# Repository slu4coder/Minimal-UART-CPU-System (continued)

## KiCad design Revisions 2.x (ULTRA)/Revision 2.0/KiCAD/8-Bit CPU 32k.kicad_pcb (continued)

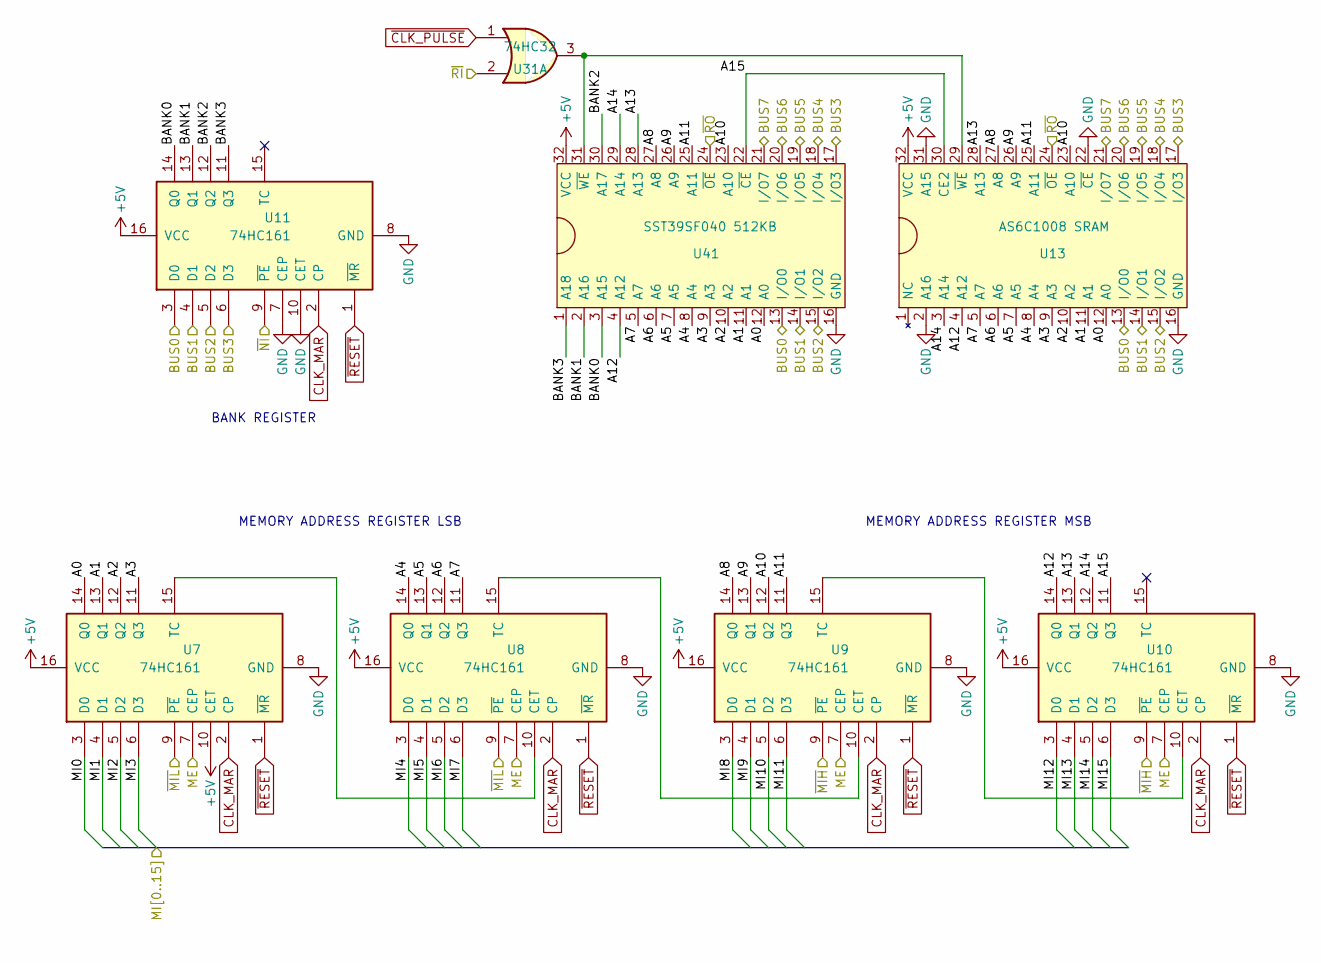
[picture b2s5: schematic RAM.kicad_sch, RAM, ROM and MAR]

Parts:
U7, U8, U9, U10, U11: 74HC161; DIP-16_W7.62mm
U13: AS6C1008 SRAM; DIP-32_W15.24mm
U31: 74HC32; DIP-14_W7.62mm
U41: SST39SF040 512KB; DIP-32_W15.24mm_Socket

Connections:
+5V: U7.10 (CET), U7.16 (VCC), U8.16 (VCC), U9.16 (VCC), U10.16 (VCC), U11.16 (VCC), U13.32 (VCC), U41.32 (VCC); also elsewhere on the board
/ALU/BUS0: U11.3 (D0), U13.13 (I/O0), U41.13 (I/O0); also elsewhere on the board
/ALU/BUS1: U11.4 (D1), U13.14 (I/O1), U41.14 (I/O1); also elsewhere on the board
/ALU/BUS2: U11.5 (D2), U13.15 (I/O2), U41.15 (I/O2); also elsewhere on the board
/ALU/BUS3: U11.6 (D3), U13.17 (I/O3), U41.17 (I/O3); also elsewhere on the board
/ALU/BUS4: U13.18 (I/O4), U41.18 (I/O4); also elsewhere on the board
/ALU/BUS5: U13.19 (I/O5), U41.19 (I/O5); also elsewhere on the board
/ALU/BUS6: U13.20 (I/O6), U41.20 (I/O6); also elsewhere on the board
/ALU/BUS7: U13.21 (I/O7), U41.21 (I/O7); also elsewhere on the board
/Control Logic/ME: U7.7 (CEP), U8.7 (CEP), U9.7 (CEP), U10.7 (CEP); also elsewhere on the board
/Control Logic/~MIH: U9.9 (~PE), U10.9 (~PE); also elsewhere on the board
/Control Logic/~MIL: U7.9 (~PE), U8.9 (~PE); also elsewhere on the board
/Control Logic/~NI: U11.9 (~PE); also elsewhere on the board
/Control Logic/~RI: U31.2; also elsewhere on the board
/Control Logic/~RO: U13.24 (~OE), U41.24 (~OE); also elsewhere on the board
/Memory/A0: U7.14 (Q0), U13.12 (A0), U41.12 (A0)
/Memory/A1: U7.13 (Q1), U13.11 (A1), U41.11 (A1)
/Memory/A2: U7.12 (Q2), U13.10 (A2), U41.10 (A2)
/Memory/A3: U7.11 (Q3), U13.9 (A3), U41.9 (A3)
/Memory/A4: U8.14 (Q0), U13.8 (A4), U41.8 (A4)
/Memory/A5: U8.13 (Q1), U13.7 (A5), U41.7 (A5)
/Memory/A6: U8.12 (Q2), U13.6 (A6), U41.6 (A6)
/Memory/A7: U8.11 (Q3), U13.5 (A7), U41.5 (A7)
/Memory/A8: U9.14 (Q0), U13.27 (A8), U41.27 (A8)
/Memory/A9: U9.13 (Q1), U13.26 (A9), U41.26 (A9)
/Memory/A10: U9.12 (Q2), U13.23 (A10), U41.23 (A10)
/Memory/A11: U9.11 (Q3), U13.25 (A11), U41.25 (A11)
/Memory/A12: U10.14 (Q0), U13.4 (A12), U41.4 (A12)
/Memory/A13: U10.13 (Q1), U13.28 (A13), U41.28 (A13)
/Memory/A14: U10.12 (Q2), U13.3 (A14), U41.29 (A14)
/Memory/A15: U10.11 (Q3), U13.30 (CE2), U41.22 (~CE)
/Memory/BANK0: U11.14 (Q0), U41.3 (A15)
/Memory/BANK1: U11.13 (Q1), U41.2 (A16)
/Memory/BANK2: U11.12 (Q2), U41.30 (A17)
/Memory/BANK3: U11.11 (Q3), U41.1 (A18)
/Memory/MI0: U7.3 (D0); also elsewhere on the board
/Memory/MI1: U7.4 (D1); also elsewhere on the board
/Memory/MI2: U7.5 (D2); also elsewhere on the board
/Memory/MI3: U7.6 (D3); also elsewhere on the board
/Memory/MI4: U8.3 (D0); also elsewhere on the board
/Memory/MI5: U8.4 (D1); also elsewhere on the board
/Memory/MI6: U8.5 (D2); also elsewhere on the board
/Memory/MI7: U8.6 (D3); also elsewhere on the board
/Memory/MI8: U9.3 (D0); also elsewhere on the board
/Memory/MI9: U9.4 (D1); also elsewhere on the board
/Memory/MI10: U9.5 (D2); also elsewhere on the board
/Memory/MI11: U9.6 (D3); also elsewhere on the board
/Memory/MI12: U10.3 (D0); also elsewhere on the board
/Memory/MI13: U10.4 (D1); also elsewhere on the board
/Memory/MI14: U10.5 (D2); also elsewhere on the board
/Memory/MI15: U10.6 (D3); also elsewhere on the board
CLK_MAR: U7.2 (CP), U8.2 (CP), U9.2 (CP), U10.2 (CP), U11.2 (CP); also elsewhere on the board
GND: U7.8 (GND), U8.8 (GND), U9.8 (GND), U10.8 (GND), U11.7 (CEP), U11.8 (GND), U11.10 (CET), U13.2 (A16), U13.16 (GND), U13.22 (~CE), U13.31 (A15), U41.16 (GND); also elsewhere on the board
unnamed: U7.15 (TC), U8.10 (CET)
unnamed: U8.15 (TC), U9.10 (CET)
unnamed: U9.15 (TC), U10.10 (CET)
unnamed: U13.29 (~WE), U31.3, U41.31 (~WE)
~CLK_PULSE: U31.1; also elsewhere on the board
~RESET: U7.1 (~MR), U8.1 (~MR), U9.1 (~MR), U10.1 (~MR), U11.1 (~MR); also elsewhere on the board

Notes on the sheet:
MEMORY ADDRESS REGISTER MSB
MEMORY ADDRESS REGISTER LSB
BANK REGISTER

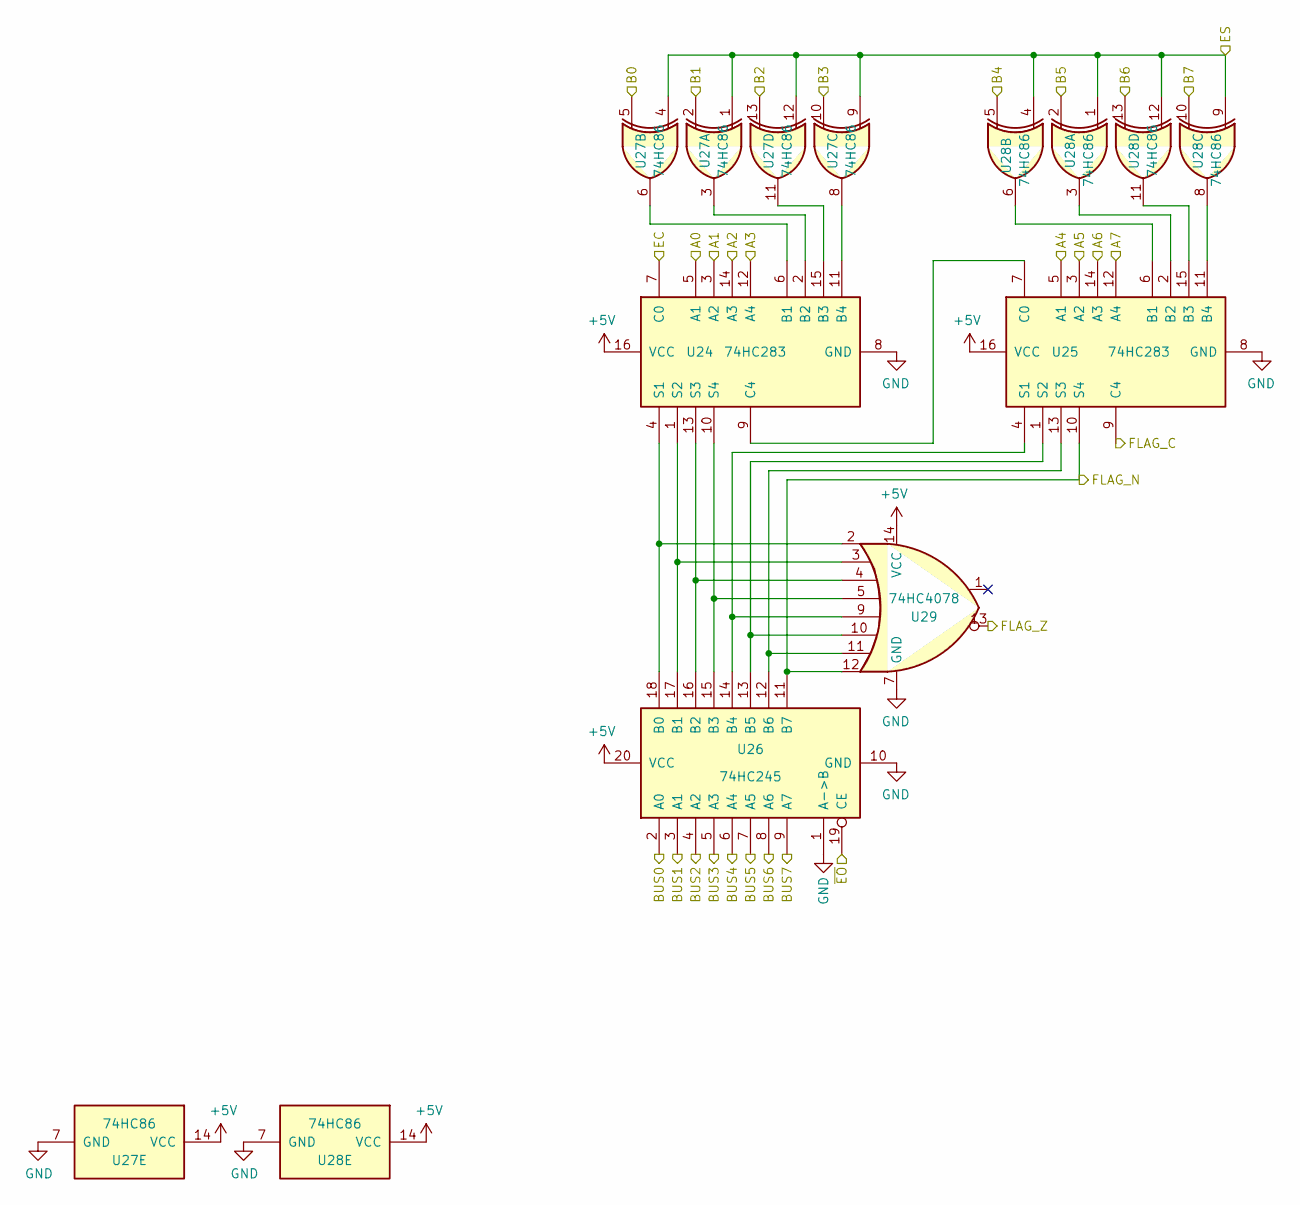
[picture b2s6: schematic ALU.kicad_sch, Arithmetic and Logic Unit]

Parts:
U24, U25: 74HC283; DIP-16_W7.62mm
U26: 74HC245; DIP-20_W7.62mm
U27, U28: 74HC86; DIP-14_W7.62mm
U29: 74HC4078; DIP-14_W7.62mm

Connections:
+5V: U24.16 (VCC), U25.16 (VCC), U26.20 (VCC), U27.14 (VCC), U28.14 (VCC), U29.14 (VCC); also elsewhere on the board
/ALU/A0: U24.5 (A1); also elsewhere on the board
/ALU/A1: U24.3 (A2); also elsewhere on the board
/ALU/A2: U24.14 (A3); also elsewhere on the board
/ALU/A3: U24.12 (A4); also elsewhere on the board
/ALU/A4: U25.5 (A1); also elsewhere on the board
/ALU/A5: U25.3 (A2); also elsewhere on the board
/ALU/A6: U25.14 (A3); also elsewhere on the board
/ALU/A7: U25.12 (A4); also elsewhere on the board
/ALU/B0: U27.5; also elsewhere on the board
/ALU/B1: U27.2; also elsewhere on the board
/ALU/B2: U27.13; also elsewhere on the board
/ALU/B3: U27.10; also elsewhere on the board
/ALU/B4: U28.5; also elsewhere on the board
/ALU/B5: U28.2; also elsewhere on the board
/ALU/B6: U28.13; also elsewhere on the board
/ALU/B7: U28.10; also elsewhere on the board
/ALU/BUS0: U26.2 (A0); also elsewhere on the board
/ALU/BUS1: U26.3 (A1); also elsewhere on the board
/ALU/BUS2: U26.4 (A2); also elsewhere on the board
/ALU/BUS3: U26.5 (A3); also elsewhere on the board
/ALU/BUS4: U26.6 (A4); also elsewhere on the board
/ALU/BUS5: U26.7 (A5); also elsewhere on the board
/ALU/BUS6: U26.8 (A6); also elsewhere on the board
/ALU/BUS7: U26.9 (A7); also elsewhere on the board
/ALU/EC: U24.7 (C0); also elsewhere on the board
/ALU/ES: U27.1, U27.4, U27.9, U27.12, U28.1, U28.4, U28.9, U28.12; also elsewhere on the board
/ALU/FLAG_C: U25.9 (C4); also elsewhere on the board
/ALU/FLAG_N: U25.10 (S4), U26.11 (B7), U29.12; also elsewhere on the board
/ALU/FLAG_Z: U29.13; also elsewhere on the board
/ALU/~EO: U26.19 (CE); also elsewhere on the board
GND: U24.8 (GND), U25.8 (GND), U26.1 (A->B), U26.10 (GND), U27.7 (GND), U28.7 (GND), U29.7 (GND); also elsewhere on the board
unnamed: U24.1 (S2), U26.17 (B1), U29.3
unnamed: U24.2 (B2), U27.3
unnamed: U24.4 (S1), U26.18 (B0), U29.2
unnamed: U24.6 (B1), U27.6
unnamed: U24.9 (C4), U25.7 (C0)
unnamed: U24.10 (S4), U26.15 (B3), U29.5
unnamed: U24.11 (B4), U27.8
unnamed: U24.13 (S3), U26.16 (B2), U29.4
unnamed: U24.15 (B3), U27.11
unnamed: U25.1 (S2), U26.13 (B5), U29.10
unnamed: U25.2 (B2), U28.3
unnamed: U25.4 (S1), U26.14 (B4), U29.9
unnamed: U25.6 (B1), U28.6
unnamed: U25.11 (B4), U28.8
unnamed: U25.13 (S3), U26.12 (B6), U29.11
unnamed: U25.15 (B3), U28.11

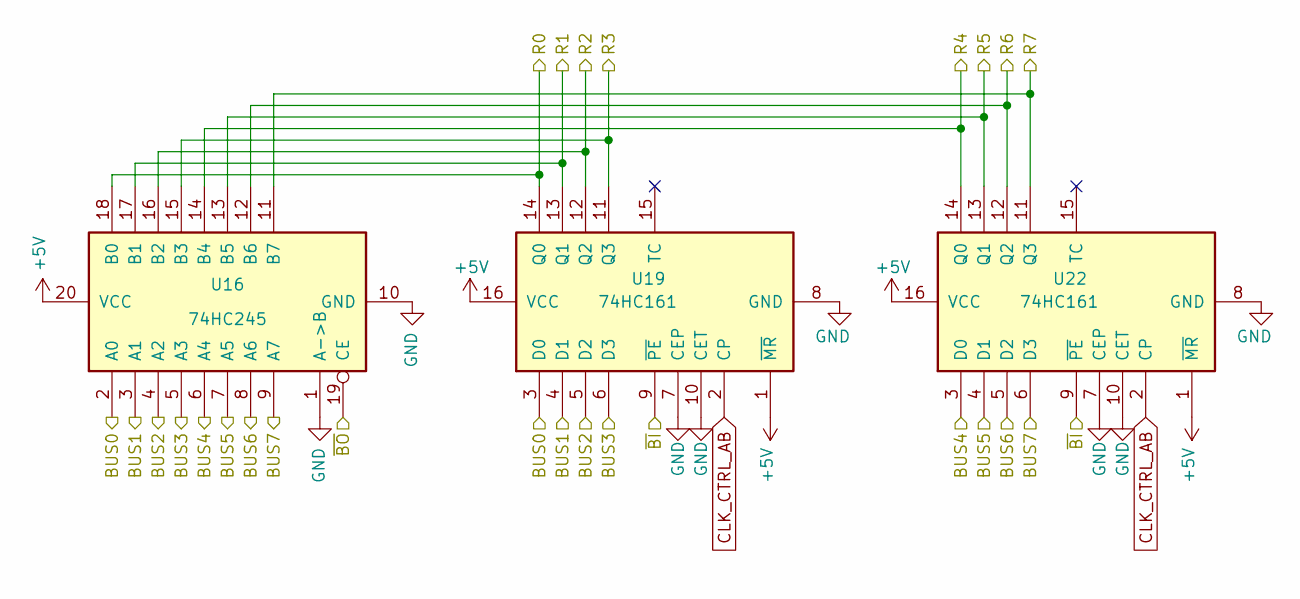
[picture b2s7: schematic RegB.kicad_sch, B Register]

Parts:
U16: 74HC245; DIP-20_W7.62mm
U19, U22: 74HC161; DIP-16_W7.62mm

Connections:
+5V: U16.20 (VCC), U19.1 (~MR), U19.16 (VCC), U22.1 (~MR), U22.16 (VCC); also elsewhere on the board
/ALU/B0: U16.18 (B0), U19.14 (Q0); also elsewhere on the board
/ALU/B1: U16.17 (B1), U19.13 (Q1); also elsewhere on the board
/ALU/B2: U16.16 (B2), U19.12 (Q2); also elsewhere on the board
/ALU/B3: U16.15 (B3), U19.11 (Q3); also elsewhere on the board
/ALU/B4: U16.14 (B4), U22.14 (Q0); also elsewhere on the board
/ALU/B5: U16.13 (B5), U22.13 (Q1); also elsewhere on the board
/ALU/B6: U16.12 (B6), U22.12 (Q2); also elsewhere on the board
/ALU/B7: U16.11 (B7), U22.11 (Q3); also elsewhere on the board
/ALU/BUS0: U16.2 (A0), U19.3 (D0); also elsewhere on the board
/ALU/BUS1: U16.3 (A1), U19.4 (D1); also elsewhere on the board
/ALU/BUS2: U16.4 (A2), U19.5 (D2); also elsewhere on the board
/ALU/BUS3: U16.5 (A3), U19.6 (D3); also elsewhere on the board
/ALU/BUS4: U16.6 (A4), U22.3 (D0); also elsewhere on the board
/ALU/BUS5: U16.7 (A5), U22.4 (D1); also elsewhere on the board
/ALU/BUS6: U16.8 (A6), U22.5 (D2); also elsewhere on the board
/ALU/BUS7: U16.9 (A7), U22.6 (D3); also elsewhere on the board
/Control Logic/~BI: U19.9 (~PE), U22.9 (~PE); also elsewhere on the board
/Control Logic/~BO: U16.19 (CE); also elsewhere on the board
CLK_CTRL_AB: U19.2 (CP), U22.2 (CP); also elsewhere on the board
GND: U16.1 (A->B), U16.10 (GND), U19.7 (CEP), U19.8 (GND), U19.10 (CET), U22.7 (CEP), U22.8 (GND), U22.10 (CET); also elsewhere on the board

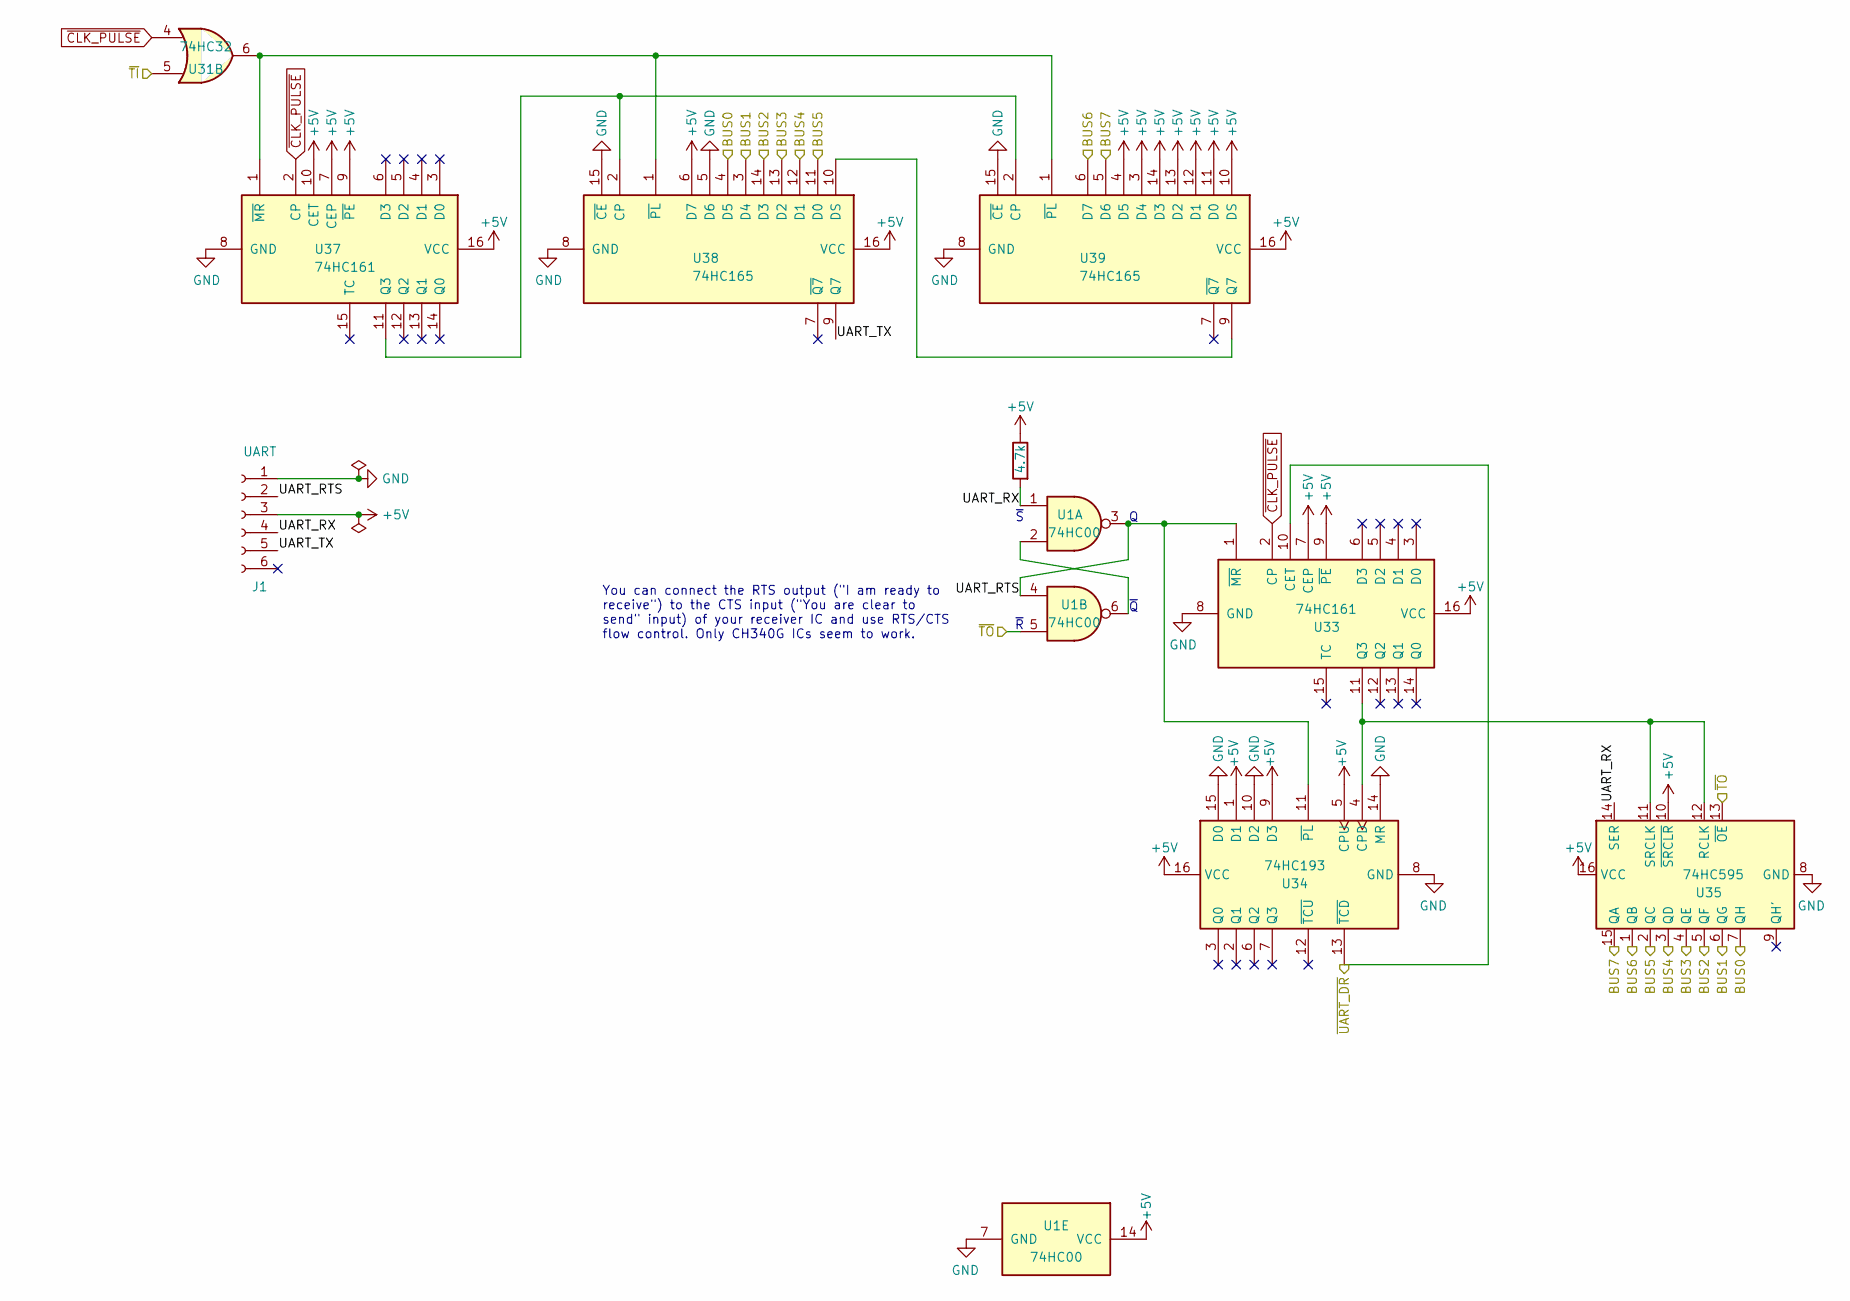
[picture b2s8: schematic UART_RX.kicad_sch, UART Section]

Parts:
J1: UART; PinSocket_1x06_P2.54mm_Vertical
R22: 4.7k; R_Axial_DIN0207_L6.3mm_D2.5mm_P7.62mm_Horizontal
U1: 74HC00; DIP-14_W7.62mm
U31: 74HC32; DIP-14_W7.62mm
U33, U37: 74HC161; DIP-16_W7.62mm
U34: 74HC193; DIP-16_W7.62mm
U35: 74HC595; DIP-16_W7.62mm
U38, U39: 74HC165; DIP-16_W7.62mm

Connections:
+5V: J1.3, R22.1, U1.14 (VCC), U33.7 (CEP), U33.9 (~PE), U33.16 (VCC), U34.1 (D1), U34.5 (CPU), U34.9 (D3), U34.16 (VCC), U35.10 (~SRCLR), U35.16 (VCC), U37.7 (CEP), U37.9 (~PE), U37.10 (CET), U37.16 (VCC), U38.6 (D7), U38.16 (VCC), U39.3 (D4), U39.4 (D5), U39.10 (DS), U39.11 (D0), U39.12 (D1), U39.13 (D2), U39.14 (D3), U39.16 (VCC); also elsewhere on the board
/ALU/BUS0: U35.7 (QH), U38.4 (D5); also elsewhere on the board
/ALU/BUS1: U35.6 (QG), U38.3 (D4); also elsewhere on the board
/ALU/BUS2: U35.5 (QF), U38.14 (D3); also elsewhere on the board
/ALU/BUS3: U35.4 (QE), U38.13 (D2); also elsewhere on the board
/ALU/BUS4: U35.3 (QD), U38.12 (D1); also elsewhere on the board
/ALU/BUS5: U35.2 (QC), U38.11 (D0); also elsewhere on the board
/ALU/BUS6: U35.1 (QB), U39.6 (D7); also elsewhere on the board
/ALU/BUS7: U35.15 (QA), U39.5 (D6); also elsewhere on the board
/Control Logic/~TI: U31.5; also elsewhere on the board
/Control Logic/~TO: U1.5, U35.13 (~OE); also elsewhere on the board
/Control Logic/~UART_DR: U33.10 (CET), U34.13 (~TCD); also elsewhere on the board
/UART/UART_RTS: J1.2, U1.3, U1.4, U33.1 (~MR), U34.11 (~PL)
/UART/UART_RX: J1.4, R22.2, U1.1, U35.14 (SER)
/UART/UART_TX: J1.5, U38.9 (Q7)
GND: J1.1, U1.7 (GND), U33.8 (GND), U34.8 (GND), U34.10 (D2), U34.14 (MR), U34.15 (D0), U35.8 (GND), U37.8 (GND), U38.5 (D6), U38.8 (GND), U38.15 (~CE), U39.8 (GND), U39.15 (~CE); also elsewhere on the board
unnamed: U1.2, U1.6
unnamed: U31.6, U37.1 (~MR), U38.1 (~PL), U39.1 (~PL)
unnamed: U33.11 (Q3), U34.4 (CPD), U35.11 (SRCLK), U35.12 (RCLK)
unnamed: U37.11 (Q3), U38.2 (CP), U39.2 (CP)
unnamed: U38.10 (DS), U39.9 (Q7)
~CLK_PULSE: U31.4, U33.2 (CP), U37.2 (CP); also elsewhere on the board

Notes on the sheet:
You can connect the RTS output ("I am ready to receive") to the CTS input ("You are clear to send" input) of your receiver IC and use RTS/CTS flow control. Only CH340G ICs seem to work.
~{Q}
~{S}
~{R}

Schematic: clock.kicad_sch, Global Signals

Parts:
R21: 470; R_Axial_DIN0207_L6.3mm_D2.5mm_P7.62mm_Horizontal
SW1: RESET; SW_PUSH_6mm
U1: 74HC00; DIP-14_W7.62mm
U31: 74HC32; DIP-14_W7.62mm
U40: 74HC02; DIP-14_W7.62mm
X1: 10MHz; Oscillator_DIP-14

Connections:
+5V: R21.1, U1.13, U31.14 (VCC), U40.14 (VCC), X1.14 (Vcc); also elsewhere on the board
CLK_CTRL_AB: U40.1; also elsewhere on the board
CLK_MAR: U40.10; also elsewhere on the board
CLK_PC: U40.4; also elsewhere on the board
GND: SW1.2, U31.7 (GND), U31.10, U31.12, U40.3, U40.6, U40.7 (GND), U40.9, X1.7 (GND); also elsewhere on the board
unnamed: U1.9, U31.9, X1.8 (OUT)
unnamed: U1.10, U31.11
unnamed: U1.11, U31.13, U40.2, U40.5, U40.8
unnamed: U1.12, U31.8
~CLK_PULSE: U1.8; also elsewhere on the board
~RESET: R21.2, SW1.1; also elsewhere on the board

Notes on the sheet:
resets SC, PC and BANK

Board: 2 copper layers, 73 parts (0 on the bottom side), 162 nets, no tracks yet.

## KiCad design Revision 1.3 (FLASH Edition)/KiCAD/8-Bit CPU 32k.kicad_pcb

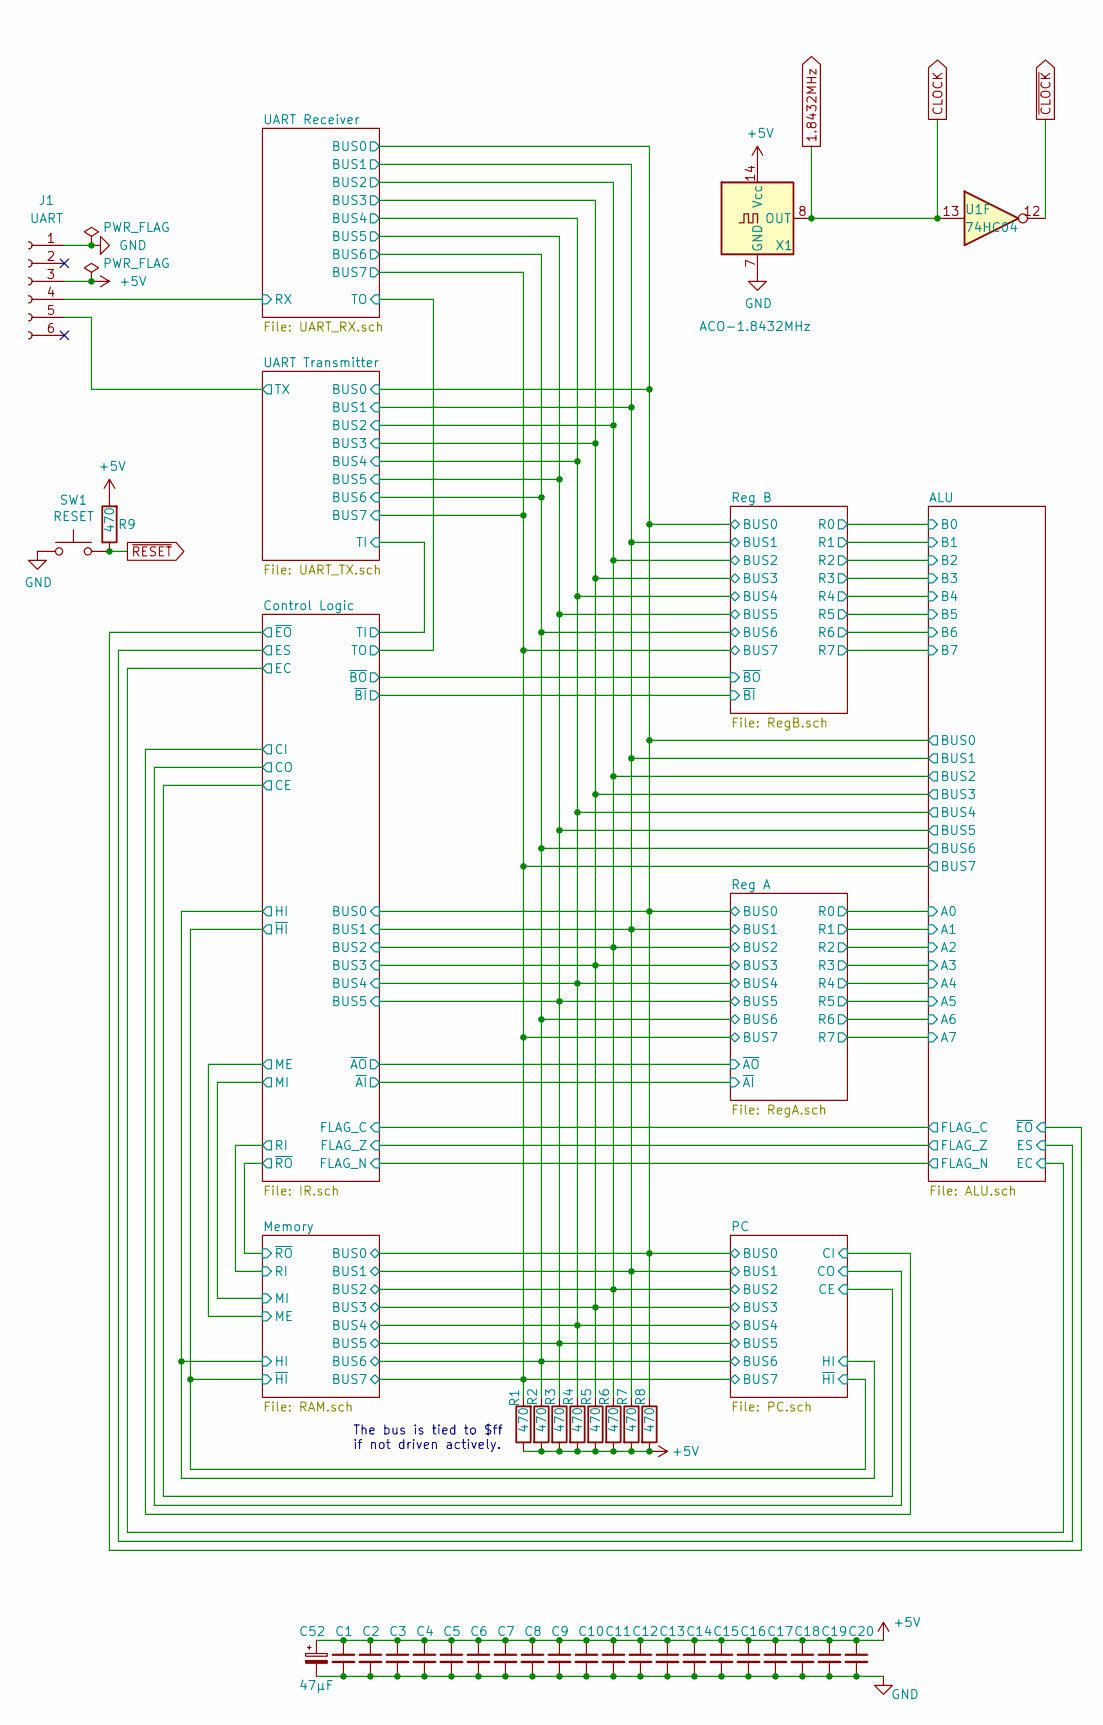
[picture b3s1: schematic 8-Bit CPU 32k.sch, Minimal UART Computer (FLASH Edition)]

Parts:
C1, C2, C3, C4, C5, C6, C7, C8, C9, C10, C11, C12, C13, C14, C15, C16, C17, C18, C19, C20: 100nF; C_Disc_D5.0mm_W2.5mm_P2.50mm
C52: 47µF; CP_Radial_D7.5mm_P2.50mm
J1: UART; PinSocket_1x06_P2.54mm_Vertical
R1, R2, R3, R4, R5, R6, R7, R8, R9: 470; R_Axial_DIN0207_L6.3mm_D2.5mm_P7.62mm_Horizontal
SW1: RESET; SW_PUSH_6mm
U1: 74HC04; DIP-14_W7.62mm
X1: ACO-1.8432MHz; Oscillator_DIP-14

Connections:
1.8432MHz: U1.13, X1.8 (OUT); also elsewhere on the board
+5V: C1.1, C2.1, C3.1, C4.1, C5.1, C6.1, C7.1, C8.1, C9.1, C10.1, C11.1, C12.1, C13.1, C14.1, C15.1, C16.1, C17.1, C18.1, C19.1, C20.1, C52.1, J1.3, R1.1, R2.2, R3.2, R4.2, R5.2, R6.2, R7.2, R8.2, R9.2, X1.14 (Vcc); also elsewhere on the board
/ALU/BUS0: R8.1; also elsewhere on the board
/ALU/BUS1: R7.1; also elsewhere on the board
/ALU/BUS2: R6.1; also elsewhere on the board
/ALU/BUS3: R5.1; also elsewhere on the board
/ALU/BUS4: R4.1; also elsewhere on the board
/ALU/BUS5: R3.1; also elsewhere on the board
/ALU/BUS6: R2.1; also elsewhere on the board
/ALU/BUS7: R1.2; also elsewhere on the board
/UART Receiver/RX: J1.4; also elsewhere on the board
/UART Transmitter/TX: J1.5; also elsewhere on the board
GND: C1.2, C2.2, C3.2, C4.2, C5.2, C6.2, C7.2, C8.2, C9.2, C10.2, C11.2, C12.2, C13.2, C14.2, C15.2, C16.2, C17.2, C18.2, C19.2, C20.2, C52.2, J1.1, SW1.1, X1.7 (GND); also elsewhere on the board
~CLOCK: U1.12; also elsewhere on the board
~RESET: R9.1, SW1.2; also elsewhere on the board

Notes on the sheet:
The bus is tied to $ff if not driven actively.

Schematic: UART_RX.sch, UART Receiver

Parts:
U1: 74HC04; DIP-14_W7.62mm
U19: 74HC08; DIP-14_W7.62mm
U20: 74HC173; DIP-16_W7.62mm
U34: 74HC161; DIP-16_W7.62mm
U35: 74HC00; DIP-14_W7.62mm
U37: 74HC193; DIP-16_W7.62mm
U39: 74HC164; DIP-14_W7.62mm
U41: 74HC245; DIP-20_W7.62mm

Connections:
1.8432MHz: U34.2, U35.13; also elsewhere on the board
+5V: U19.14 (VCC), U20.16, U34.7, U34.9, U34.10, U34.16, U35.14 (VCC), U37.5, U37.9, U37.15, U37.16, U39.2 (DSB), U39.9 (~MR), U39.14 (VCC), U41.1 (A->B), U41.20 (VCC); also elsewhere on the board
/ALU/BUS0: U41.11 (B7); also elsewhere on the board
/ALU/BUS1: U41.12 (B6); also elsewhere on the board
/ALU/BUS2: U41.13 (B5); also elsewhere on the board
/ALU/BUS3: U41.14 (B4); also elsewhere on the board
/ALU/BUS4: U41.15 (B3); also elsewhere on the board
/ALU/BUS5: U41.16 (B2); also elsewhere on the board
/ALU/BUS6: U41.17 (B1); also elsewhere on the board
/ALU/BUS7: U41.18 (B0); also elsewhere on the board
/ALU/FLAG_Z: U19.6; also elsewhere on the board
/Control Logic/TO: U35.10; also elsewhere on the board
/UART Receiver/RX: U35.1, U39.1 (DSA); also elsewhere on the board
GND: U19.7 (GND), U20.1, U20.2, U20.8, U20.9, U20.10, U20.11, U20.12, U20.13, U20.15, U34.8, U35.7 (GND), U37.1, U37.8, U37.10, U37.14, U39.7 (GND), U41.10 (GND); also elsewhere on the board
unnamed: U1.5, U19.10, U37.13
unnamed: U1.6, U20.14
unnamed: U1.10, U35.12
unnamed: U1.11, U35.8, U41.19 (CE)
unnamed 103: U19.1; also elsewhere on the board
unnamed 104: U19.2; also elsewhere on the board
unnamed 105: U19.12; also elsewhere on the board
unnamed 106: U19.13; also elsewhere on the board
unnamed: U19.3, U19.4
unnamed: U19.8, U34.1
unnamed: U19.9, U35.3, U35.4, U37.11
unnamed: U19.5, U19.11
unnamed: U20.3, U35.9
unnamed: U34.11, U37.4, U39.8 (CP)
unnamed: U35.2, U35.6
unnamed: U35.5, U35.11
unnamed: U39.3 (Q0), U41.2 (A0)
unnamed: U39.4 (Q1), U41.3 (A1)
unnamed: U39.5 (Q2), U41.4 (A2)
unnamed: U39.6 (Q3), U41.5 (A3)
unnamed: U39.10 (Q4), U41.6 (A4)
unnamed: U39.11 (Q5), U41.7 (A5)
unnamed: U39.12 (Q6), U41.8 (A6)
unnamed: U39.13 (Q7), U41.9 (A7)
~CLOCK: U20.7; also elsewhere on the board

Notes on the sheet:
~RESET
~SET
AND from ALU
SYNC_DATA_READY

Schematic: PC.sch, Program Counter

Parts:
U46, U49, U51, U52: 74HC161; DIP-16_W7.62mm
U48: 74HC00; DIP-14_W7.62mm
U50, U53: 74HC245; DIP-20_W7.62mm

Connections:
1.8432MHz: U46.2, U49.2, U51.2, U52.2; also elsewhere on the board
+5V: U46.16, U48.14 (VCC), U49.16, U50.20 (VCC), U51.16, U52.16, U53.20 (VCC); also elsewhere on the board
/ALU/BUS0: U49.3, U50.2 (A0), U52.3, U53.2 (A0); also elsewhere on the board
/ALU/BUS1: U49.4, U50.3 (A1), U52.4, U53.3 (A1); also elsewhere on the board
/ALU/BUS2: U49.5, U50.4 (A2), U52.5, U53.4 (A2); also elsewhere on the board
/ALU/BUS3: U49.6, U50.5 (A3), U52.6, U53.5 (A3); also elsewhere on the board
/ALU/BUS4: U46.3, U50.6 (A4), U51.3, U53.6 (A4); also elsewhere on the board
/ALU/BUS5: U46.4, U50.7 (A5), U51.4, U53.7 (A5); also elsewhere on the board
/ALU/BUS6: U46.5, U50.8 (A6), U51.5, U53.8 (A6); also elsewhere on the board
/ALU/BUS7: U46.6, U50.9 (A7), U51.6, U53.9 (A7); also elsewhere on the board
/Control Logic/CE: U46.7, U49.7, U51.7, U52.7, U52.10; also elsewhere on the board
/Control Logic/CI: U48.10, U48.12; also elsewhere on the board
/Control Logic/CO: U48.2, U48.4; also elsewhere on the board
/Control Logic/HI: U48.1, U48.13; also elsewhere on the board
/Control Logic/~HI: U48.5, U48.9; also elsewhere on the board
GND: U46.8, U48.7 (GND), U49.8, U50.1 (A->B), U50.10 (GND), U51.8, U52.8, U53.1 (A->B), U53.10 (GND); also elsewhere on the board
unnamed: U46.9, U48.11, U49.9
unnamed: U46.10, U49.15
unnamed: U46.11, U50.11 (B7)
unnamed: U46.12, U50.12 (B6)
unnamed: U46.13, U50.13 (B5)
unnamed: U46.14, U50.14 (B4)
unnamed: U48.3, U50.19 (CE)
unnamed: U48.6, U53.19 (CE)
unnamed: U48.8, U51.9, U52.9
unnamed: U49.10, U51.15
unnamed: U49.11, U50.15 (B3)
unnamed: U49.12, U50.16 (B2)
unnamed: U49.13, U50.17 (B1)
unnamed: U49.14, U50.18 (B0)
unnamed: U51.10, U52.15
unnamed: U51.11, U53.11 (B7)
unnamed: U51.12, U53.12 (B6)
unnamed: U51.13, U53.13 (B5)
unnamed: U51.14, U53.14 (B4)
unnamed: U52.11, U53.15 (B3)
unnamed: U52.12, U53.16 (B2)
unnamed: U52.13, U53.17 (B1)
unnamed: U52.14, U53.18 (B0)
~RESET: U46.1, U49.1, U51.1, U52.1; also elsewhere on the board

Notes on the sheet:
~COH
~COL
~CIL
~CIH

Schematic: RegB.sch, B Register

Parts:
U10, U17: 74HC173; DIP-16_W7.62mm
U23: 74HC245; DIP-20_W7.62mm

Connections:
1.8432MHz: U10.7, U17.7; also elsewhere on the board
+5V: U10.16, U17.16, U23.1 (A->B), U23.20 (VCC); also elsewhere on the board
/ALU/B0: U17.3, U23.2 (A0); also elsewhere on the board
/ALU/B1: U17.4, U23.3 (A1); also elsewhere on the board
/ALU/B2: U17.5, U23.4 (A2); also elsewhere on the board
/ALU/B3: U17.6, U23.5 (A3); also elsewhere on the board
/ALU/B4: U10.3, U23.6 (A4); also elsewhere on the board
/ALU/B5: U10.4, U23.7 (A5); also elsewhere on the board
/ALU/B6: U10.5, U23.8 (A6); also elsewhere on the board
/ALU/B7: U10.6, U23.9 (A7); also elsewhere on the board
/ALU/BUS0: U17.14, U23.18 (B0); also elsewhere on the board
/ALU/BUS1: U17.13, U23.17 (B1); also elsewhere on the board
/ALU/BUS2: U17.12, U23.16 (B2); also elsewhere on the board
/ALU/BUS3: U17.11, U23.15 (B3); also elsewhere on the board
/ALU/BUS4: U10.14, U23.14 (B4); also elsewhere on the board
/ALU/BUS5: U10.13, U23.13 (B5); also elsewhere on the board
/ALU/BUS6: U10.12, U23.12 (B6); also elsewhere on the board
/ALU/BUS7: U10.11, U23.11 (B7); also elsewhere on the board
/Control Logic/~BI: U10.9, U10.10, U17.9, U17.10; also elsewhere on the board
/Control Logic/~BO: U23.19 (CE); also elsewhere on the board
GND: U10.1, U10.2, U10.8, U10.15, U17.1, U17.2, U17.8, U17.15, U23.10 (GND); also elsewhere on the board

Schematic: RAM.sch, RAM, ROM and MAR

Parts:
U1: 74HC04; DIP-14_W7.62mm
U26, U28, U30, U33: 74HC161; DIP-16_W7.62mm
U31: SST39SF010A ROM; DIP-32_W15.24mm_Socket
U32: CY62256 32k RAM; DIP-28_W15.24mm
U44: 74HC00; DIP-14_W7.62mm

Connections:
1.8432MHz: U26.2, U28.2, U30.2, U33.2, U44.10, U44.13; also elsewhere on the board
+5V: U26.1, U26.16, U28.1, U28.16, U30.1, U30.16, U31.32, U32.28, U33.1, U33.16, U44.14 (VCC); also elsewhere on the board
/ALU/BUS0: U28.3, U31.13, U32.11, U33.3; also elsewhere on the board
/ALU/BUS1: U28.4, U31.14, U32.12, U33.4; also elsewhere on the board
/ALU/BUS2: U28.5, U31.15, U32.13, U33.5; also elsewhere on the board
/ALU/BUS3: U28.6, U31.17, U32.15, U33.6; also elsewhere on the board
/ALU/BUS4: U26.3, U30.3, U31.18, U32.16; also elsewhere on the board
/ALU/BUS5: U26.4, U30.4, U31.19, U32.17; also elsewhere on the board
/ALU/BUS6: U26.5, U30.5, U31.20, U32.18; also elsewhere on the board
/ALU/BUS7: U26.6, U30.6, U31.21, U32.19; also elsewhere on the board
/Control Logic/CE: U26.7, U28.7, U30.7, U33.7, U33.10; also elsewhere on the board
/Control Logic/HI: U44.5; also elsewhere on the board
/Control Logic/MI: U44.2, U44.4; also elsewhere on the board
/Control Logic/RI: U44.9; also elsewhere on the board
/Control Logic/TI: U44.12; also elsewhere on the board
/Control Logic/~HI: U44.1; also elsewhere on the board
/Control Logic/~RO: U31.24, U32.22; also elsewhere on the board
/Memory/M0: U31.12, U32.21, U33.14
/Memory/M1: U31.11, U32.23, U33.13
/Memory/M2: U31.10, U32.24, U33.12
/Memory/M3: U31.9, U32.25, U33.11
/Memory/M4: U30.14, U31.8, U32.26
/Memory/M5: U30.13, U31.7, U32.1
/Memory/M6: U30.12, U31.6, U32.2
/Memory/M7: U30.11, U31.5, U32.3
/Memory/M8: U28.14, U31.27, U32.4
/Memory/M9: U28.13, U31.26, U32.5
/Memory/M10: U28.12, U31.23, U32.6
/Memory/M11: U28.11, U31.25, U32.7
/Memory/M12: U26.14, U31.4, U32.8
/Memory/M13: U26.13, U31.28, U32.9
/Memory/M14: U26.12, U31.29, U32.10
/Memory/M15: U1.9, U26.11, U31.22
GND: U26.8, U28.8, U30.8, U31.2, U31.3, U31.16, U32.14, U33.8, U44.7 (GND); also elsewhere on the board
unnamed: U1.8, U32.20
unnamed: U26.9, U28.9, U44.6
unnamed: U26.10, U28.15
unnamed: U28.10, U30.15
unnamed: U30.9, U33.9, U44.3
unnamed: U30.10, U33.15
unnamed: U31.31, U32.27, U44.8
unnamed 129: U44.11; also elsewhere on the board

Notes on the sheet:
~MIL
~MIH
~ROM_CE
~RAM_CE
NAND used in TX
A separate reset of the MAR is not needed. During the time RESET is pressed, the clock runs with SC=0 and PC=0. This ensures that with CO|MI MAL=0.
Writing only during second clockphase. ~RI~ alone would be valid even after the clock phase ended -> not good!

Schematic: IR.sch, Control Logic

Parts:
C21, C24: 200pF; C_Disc_D5.0mm_W2.5mm_P2.50mm
C22, C23: 0pF; C_Disc_D5.0mm_W2.5mm_P2.50mm
U1: 74HC04; DIP-14_W7.62mm
U5, U6, U8: 74HC173; DIP-16_W7.62mm
U7: SST39SF010A MSB; DIP-32_W15.24mm_Socket
U9: SST39SF010A LSB; DIP-32_W15.24mm_Socket
U11: 74HC161; DIP-16_W7.62mm
U40: 74HC08; DIP-14_W7.62mm

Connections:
1.8432MHz: U5.7, U6.7, U8.7; also elsewhere on the board
+5V: U1.14 (VCC), U5.16, U6.16, U7.31, U7.32, U8.16, U9.31, U9.32, U11.7, U11.9, U11.10, U11.16, U40.14; also elsewhere on the board
/ALU/BUS0: U8.14; also elsewhere on the board
/ALU/BUS1: U8.13; also elsewhere on the board
/ALU/BUS2: U8.12; also elsewhere on the board
/ALU/BUS3: U8.11; also elsewhere on the board
/ALU/BUS4: U6.14; also elsewhere on the board
/ALU/BUS5: U6.13; also elsewhere on the board
/ALU/EC: U7.15; also elsewhere on the board
/ALU/ES: U7.14; also elsewhere on the board
/ALU/FLAG_C: U5.13; also elsewhere on the board
/ALU/FLAG_N: U5.12; also elsewhere on the board
/ALU/FLAG_Z: U5.14; also elsewhere on the board
/ALU/~EO: U5.9, U5.10, U7.13; also elsewhere on the board
/Control Logic/CE: U1.3, U7.19; also elsewhere on the board
/Control Logic/CI: U7.21; also elsewhere on the board
/Control Logic/CO: U7.20; also elsewhere on the board
/Control Logic/HI: C23.2, U1.1, U9.21, U40.9; also elsewhere on the board
/Control Logic/MI: U9.20; also elsewhere on the board
/Control Logic/RI: C24.2, U9.19; also elsewhere on the board
/Control Logic/TI: U40.8; also elsewhere on the board
/Control Logic/TO: U40.3; also elsewhere on the board
/Control Logic/~AI: U9.17; also elsewhere on the board
/Control Logic/~AO: U9.15; also elsewhere on the board
/Control Logic/~BI: U9.14; also elsewhere on the board
/Control Logic/~BO: U9.13; also elsewhere on the board
/Control Logic/~HI: U1.2, U6.9, U8.9, U40.2; also elsewhere on the board
/Control Logic/~RO: U9.18; also elsewhere on the board
GND: C21.1, C22.1, C23.1, C24.1, U1.7 (GND), U5.1, U5.2, U5.8, U5.11, U5.15, U6.1, U6.2, U6.8, U6.11, U6.12, U6.15, U7.2, U7.3, U7.16, U7.22, U7.24, U7.28, U7.29, U8.1, U8.2, U8.8, U8.15, U9.2, U9.3, U9.16, U9.22, U9.24, U9.28, U9.29, U11.8, U40.7, U40.12, U40.13; also elsewhere on the board
unnamed: C21.2, U7.18, U40.1, U40.10
unnamed: C22.2, U7.17, U40.5
unnamed: U1.4, U6.10, U8.10
unnamed: U5.3, U7.23, U9.23
unnamed: U5.4, U7.25, U9.25
unnamed: U5.5, U7.4, U9.4
unnamed: U6.3, U7.27, U9.27
unnamed: U6.4, U7.26, U9.26
unnamed: U7.5, U8.6, U9.5
unnamed: U7.6, U8.5, U9.6
unnamed: U7.7, U8.4, U9.7
unnamed: U7.8, U8.3, U9.8
unnamed: U11.1, U40.6
unnamed: U7.9, U9.9, U11.11
unnamed: U7.10, U9.10, U11.12
unnamed: U7.11, U9.11, U11.13
unnamed: U7.12, U9.12, U11.14
~CLOCK: U11.2; also elsewhere on the board
~RESET: U40.4; also elsewhere on the board

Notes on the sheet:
~FI~ together with ~EO~
~IC
The caps suppress false triggering of level- triggered control signals due to switching spikes.
Instruction Step Counter
Instruction Register
Flags Register
